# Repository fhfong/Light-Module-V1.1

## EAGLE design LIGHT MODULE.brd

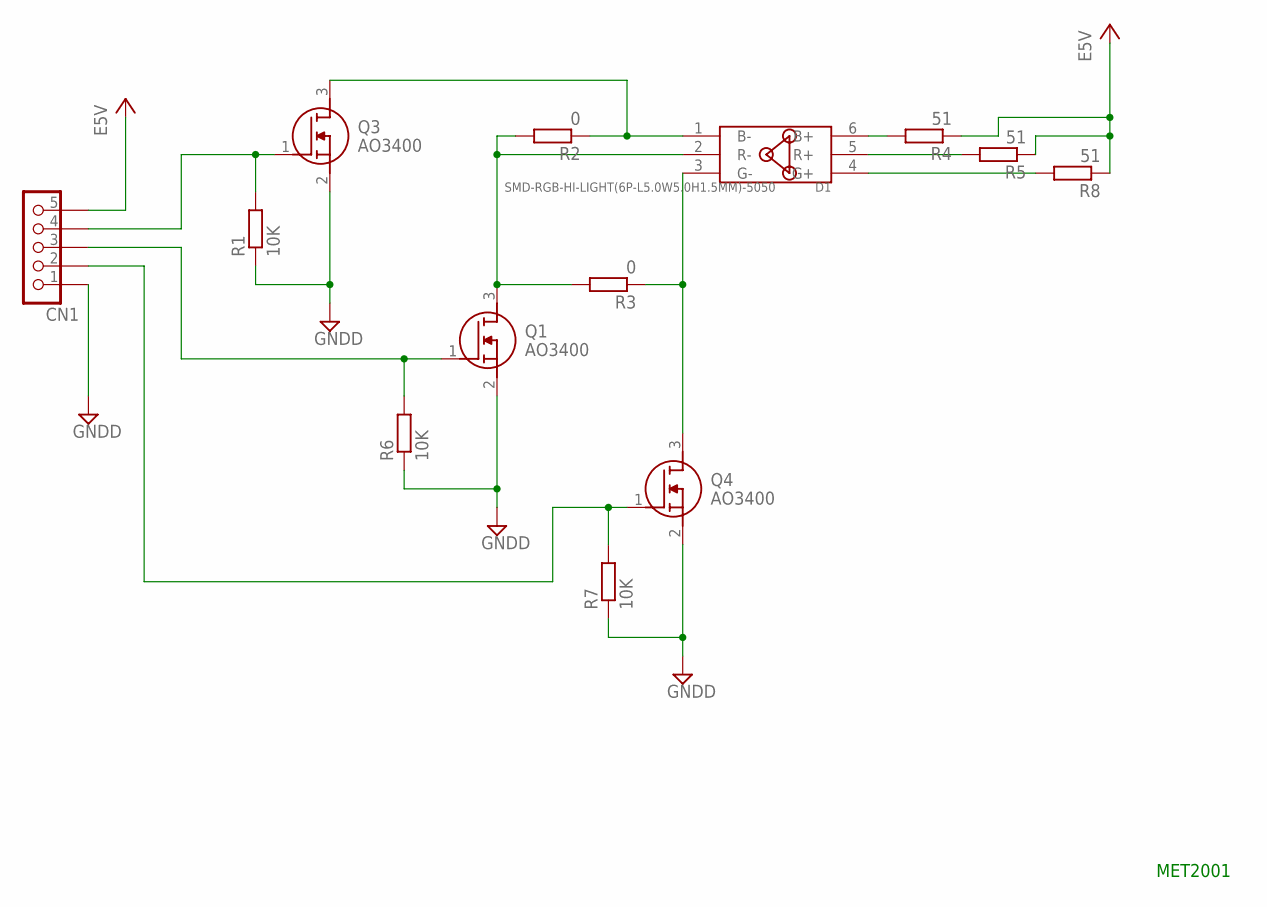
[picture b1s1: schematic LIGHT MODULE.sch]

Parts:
CN1: HEADER1X5; HEADER_1X5
D1: SMD-RGB-HI-LIGHT(6P-L5.0W5.0H1.5MM)-5050; LED6-SMD-5050
Q1, Q3, Q4: AO3400; SOT95P280X125-3N
R1, R6, R7: 10K; R0805
R2, R3: 0; R0805
R4, R5, R8: 51; R0805

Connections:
+5VA: CN1.5, R4.1, R5.1, R8.1
GNDD: CN1.1, Q1.2 (S), Q3.2 (S), Q4.2 (S), R1.1, R6.1, R7.1
unnamed: CN1.4, Q3.1 (G), R1.2
unnamed: D1.4 (G+), R8.2
unnamed: D1.5 (R+), R5.2
unnamed: D1.6 (B+), R4.2
unnamed: CN1.3, Q1.1 (G), R6.2
unnamed: D1.1 (B-), Q3.3 (D), R2.1
unnamed: D1.2 (R-), Q1.3 (D), R2.2, R3.2
unnamed: D1.3 (G-), Q4.3 (D), R3.1
unnamed: CN1.2, Q4.1 (G), R7.2

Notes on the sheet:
MET2001

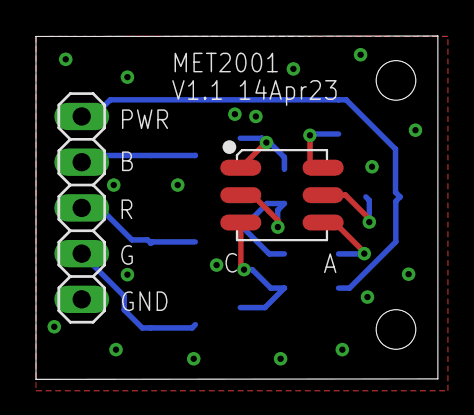
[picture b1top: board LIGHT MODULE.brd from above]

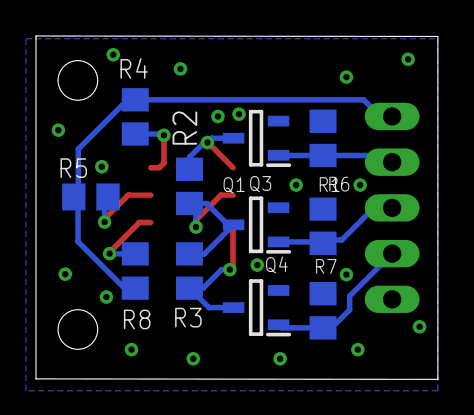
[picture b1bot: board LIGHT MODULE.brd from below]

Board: 2 copper layers, 22.3 x 19.1 mm, 13 parts (11 on the bottom side), 11 nets.

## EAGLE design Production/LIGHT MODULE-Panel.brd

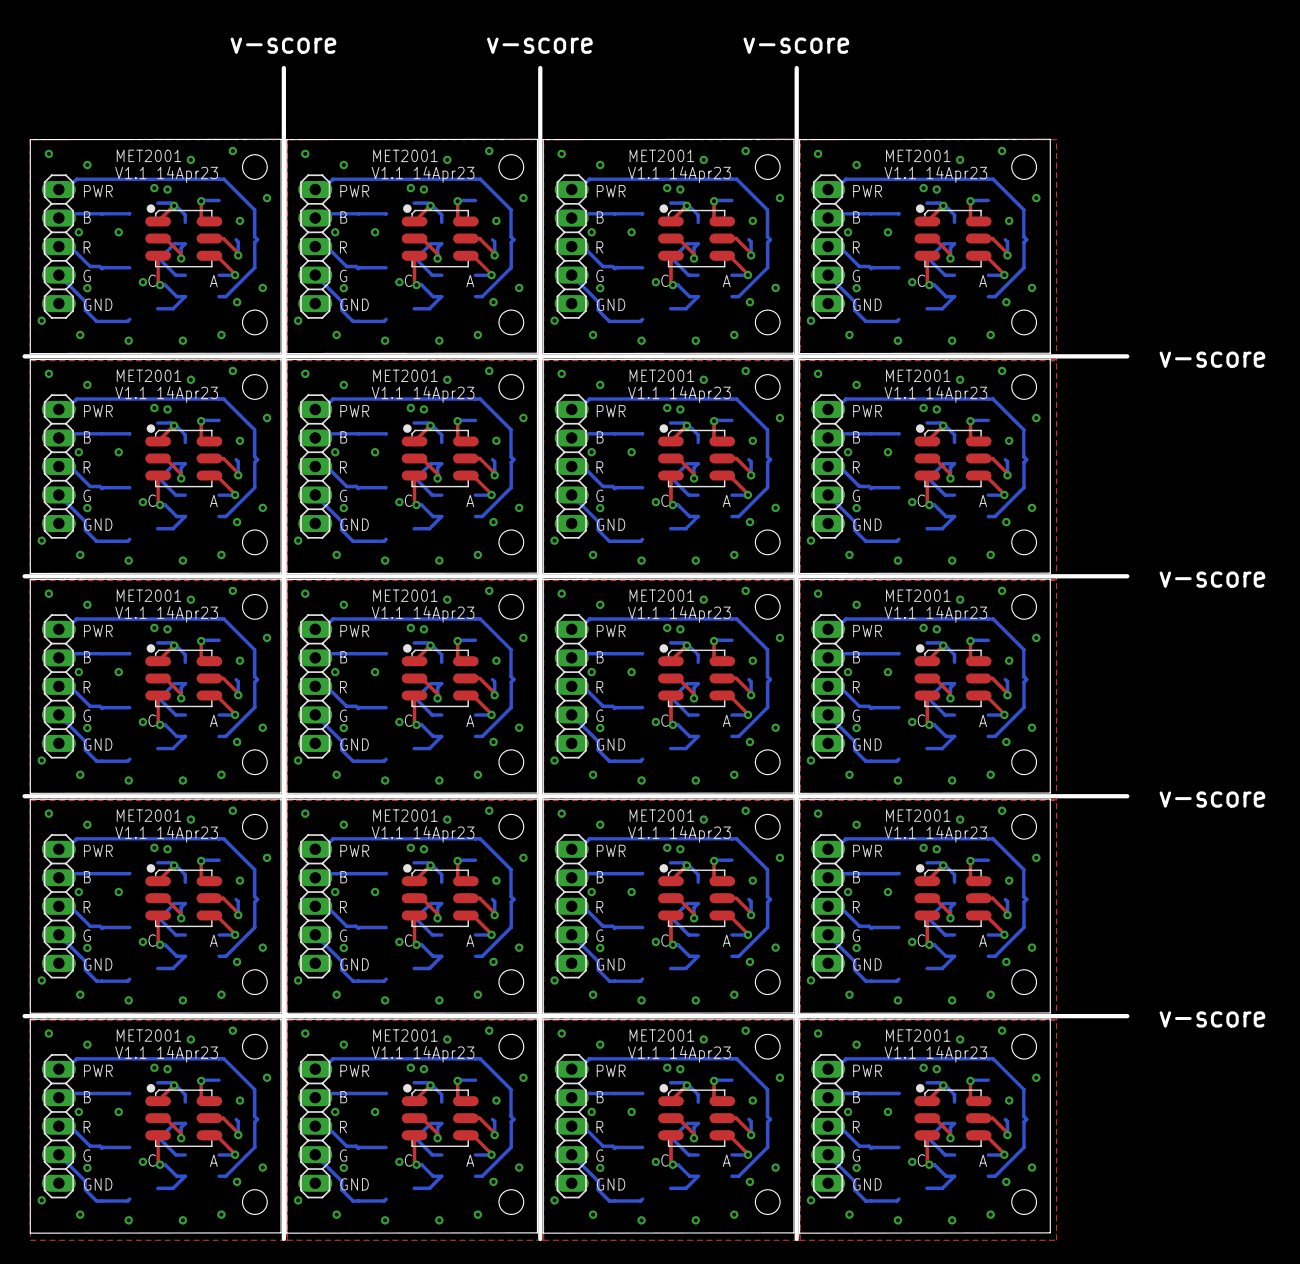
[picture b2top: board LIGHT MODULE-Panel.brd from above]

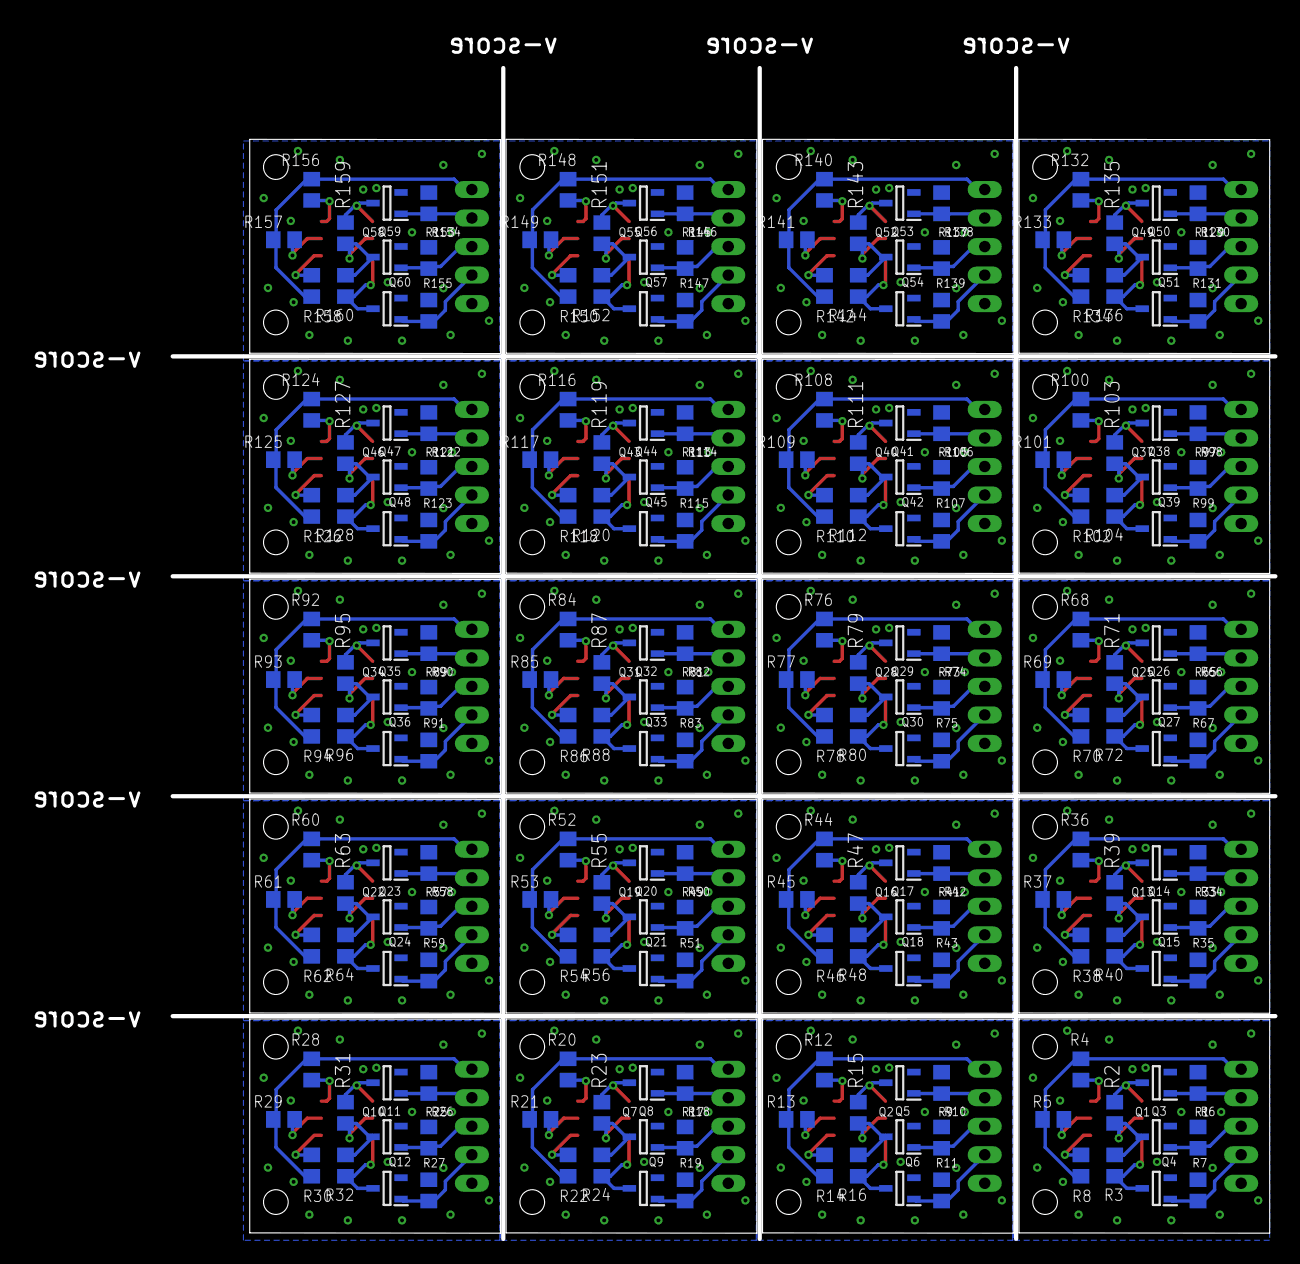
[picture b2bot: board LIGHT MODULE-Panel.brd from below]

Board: 2 copper layers, 111.4 x 108.1 mm, 260 parts (220 on the bottom side), 220 nets.

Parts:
CN1, CN2, CN3, CN4, CN5, CN6, CN7, CN8, CN9, CN10, CN11, CN12, CN13, CN14, CN15, CN16, CN17, CN18, CN19, CN20: HEADER_1X5
D1, D2, D3, D4, D5, D6, D7, D8, D9, D10, D11, D12, D13, D14, D15, D16, D17, D18, D19, D20: SMD-RGB-HI-LIGHT(6P-L5.0W5.0*H1.5MM)-5050; LED6-SMD-5050
Q1, Q2, Q3, Q4, Q5, Q6, Q7, Q8, Q9, Q10, Q11, Q12, Q13, Q14, Q15, Q16, Q17, Q18, Q19, Q20, Q21, Q22, Q23, Q24, Q25, Q26, Q27, Q28, Q29, Q30, Q31, Q32, Q33, Q34, Q35, Q36, Q37, Q38, Q39, Q40, Q41, Q42, Q43, Q44, Q45, Q46, Q47, Q48, Q49, Q50, Q51, Q52, Q53, Q54, Q55, Q56, Q57, Q58, Q59, Q60: AO3400; SOT95P280X125-3N
R1, R6, R7, R9, R10, R11, R17, R18, R19, R25, R26, R27, R33, R34, R35, R41, R42, R43, R49, R50, R51, R57, R58, R59, R65, R66, R67, R73, R74, R75, R81, R82, R83, R89, R90, R91, R97, R98, R99, R105, R106, R107, R113, R114, R115, R121, R122, R123, R129, R130, R131, R137, R138, R139, R145, R146, R147, R153, R154, R155: 10K; R0805
R2, R3, R15, R16, R23, R24, R31, R32, R39, R40, R47, R48, R55, R56, R63, R64, R71, R72, R79, R80, R87, R88, R95, R96, R103, R104, R111, R112, R119, R120, R127, R128, R135, R136, R143, R144, R151, R152, R159, R160: 0; R0805
R4, R5, R8, R12, R13, R14, R20, R21, R22, R28, R29, R30, R36, R37, R38, R44, R45, R46, R52, R53, R54, R60, R61, R62, R68, R69, R70, R76, R77, R78, R84, R85, R86, R92, R93, R94, R100, R101, R102, R108, R109, R110, R116, R117, R118, R124, R125, R126, R132, R133, R134, R140, R141, R142, R148, R149, R150, R156, R157, R158: 51; R0805

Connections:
+5VA: CN1.5, R4.1, R5.1, R8.1
+5VA1: CN2.5, R12.1, R13.1, R14.1
+5VA2: CN3.5, R20.1, R21.1, R22.1
+5VA3: CN4.5, R28.1, R29.1, R30.1
+5VA4: CN5.5, R36.1, R37.1, R38.1
+5VA5: CN6.5, R44.1, R45.1, R46.1
+5VA6: CN7.5, R52.1, R53.1, R54.1
+5VA7: CN8.5, R60.1, R61.1, R62.1
+5VA8: CN9.5, R68.1, R69.1, R70.1
+5VA9: CN10.5, R76.1, R77.1, R78.1
+5VA10: CN11.5, R84.1, R85.1, R86.1
+5VA11: CN12.5, R92.1, R93.1, R94.1
+5VA12: CN13.5, R100.1, R101.1, R102.1
+5VA13: CN14.5, R108.1, R109.1, R110.1
+5VA14: CN15.5, R116.1, R117.1, R118.1
+5VA15: CN16.5, R124.1, R125.1, R126.1
+5VA16: CN17.5, R132.1, R133.1, R134.1
+5VA17: CN18.5, R140.1, R141.1, R142.1
+5VA18: CN19.5, R148.1, R149.1, R150.1
+5VA19: CN20.5, R156.1, R157.1, R158.1
GNDD: CN1.1, Q1.2, Q3.2, Q4.2, R1.1, R6.1, R7.1
GNDD1: CN2.1, Q2.2, Q5.2, Q6.2, R9.1, R10.1, R11.1
GNDD2: CN3.1, Q7.2, Q8.2, Q9.2, R17.1, R18.1, R19.1
GNDD3: CN4.1, Q10.2, Q11.2, Q12.2, R25.1, R26.1, R27.1
GNDD4: CN5.1, Q13.2, Q14.2, Q15.2, R33.1, R34.1, R35.1
GNDD5: CN6.1, Q16.2, Q17.2, Q18.2, R41.1, R42.1, R43.1
GNDD6: CN7.1, Q19.2, Q20.2, Q21.2, R49.1, R50.1, R51.1
GNDD7: CN8.1, Q22.2, Q23.2, Q24.2, R57.1, R58.1, R59.1
GNDD8: CN9.1, Q25.2, Q26.2, Q27.2, R65.1, R66.1, R67.1
GNDD9: CN10.1, Q28.2, Q29.2, Q30.2, R73.1, R74.1, R75.1
GNDD10: CN11.1, Q31.2, Q32.2, Q33.2, R81.1, R82.1, R83.1
GNDD11: CN12.1, Q34.2, Q35.2, Q36.2, R89.1, R90.1, R91.1
GNDD12: CN13.1, Q37.2, Q38.2, Q39.2, R97.1, R98.1, R99.1
GNDD13: CN14.1, Q40.2, Q41.2, Q42.2, R105.1, R106.1, R107.1
GNDD14: CN15.1, Q43.2, Q44.2, Q45.2, R113.1, R114.1, R115.1
GNDD15: CN16.1, Q46.2, Q47.2, Q48.2, R121.1, R122.1, R123.1
GNDD16: CN17.1, Q49.2, Q50.2, Q51.2, R129.1, R130.1, R131.1
GNDD17: CN18.1, Q52.2, Q53.2, Q54.2, R137.1, R138.1, R139.1
GNDD18: CN19.1, Q55.2, Q56.2, Q57.2, R145.1, R146.1, R147.1
GNDD19: CN20.1, Q58.2, Q59.2, Q60.2, R153.1, R154.1, R155.1
unnamed: CN1.4, Q3.1, R1.2
unnamed: D1.4, R8.2
unnamed: D1.5, R5.2
unnamed: CN2.4, Q5.1, R9.2
unnamed: D1.6, R4.2
unnamed: CN1.3, Q1.1, R6.2
unnamed: D1.1, Q3.3, R2.1
unnamed: D1.2, Q1.3, R2.2, R3.2
unnamed: D1.3, Q4.3, R3.1
unnamed: CN2.3, Q2.1, R10.2
unnamed: D2.1, Q5.3, R15.1
unnamed: D2.2, Q2.3, R15.2, R16.2
unnamed: D2.3, Q6.3, R16.1
unnamed: CN2.2, Q6.1, R11.2
unnamed: CN1.2, Q4.1, R7.2
unnamed: D2.4, R14.2
unnamed: D2.5, R13.2
unnamed: D2.6, R12.2
unnamed: CN3.4, Q8.1, R17.2
unnamed: CN3.3, Q7.1, R18.2
unnamed: D3.1, Q8.3, R23.1
unnamed: D3.2, Q7.3, R23.2, R24.2
unnamed: D3.3, Q9.3, R24.1
unnamed: CN3.2, Q9.1, R19.2
unnamed: D3.4, R22.2
unnamed: D3.5, R21.2
unnamed: D3.6, R20.2
unnamed: CN4.4, Q11.1, R25.2
unnamed: CN4.3, Q10.1, R26.2
unnamed: D4.1, Q11.3, R31.1
unnamed: D4.2, Q10.3, R31.2, R32.2
unnamed: D4.3, Q12.3, R32.1
unnamed: CN4.2, Q12.1, R27.2
unnamed: D4.4, R30.2
unnamed: D4.5, R29.2
unnamed: D4.6, R28.2
unnamed: CN5.4, Q14.1, R33.2
unnamed: CN5.3, Q13.1, R34.2
unnamed: D5.1, Q14.3, R39.1
unnamed: D5.2, Q13.3, R39.2, R40.2
unnamed: D5.3, Q15.3, R40.1
unnamed: CN5.2, Q15.1, R35.2
unnamed: D5.4, R38.2
unnamed: D5.5, R37.2
unnamed: D5.6, R36.2
unnamed: CN6.4, Q17.1, R41.2
unnamed: CN6.3, Q16.1, R42.2
unnamed: D6.1, Q17.3, R47.1
unnamed: D6.2, Q16.3, R47.2, R48.2
unnamed: D6.3, Q18.3, R48.1
unnamed: CN6.2, Q18.1, R43.2
unnamed: D6.4, R46.2
unnamed: D6.5, R45.2
unnamed: D6.6, R44.2
unnamed: CN7.4, Q20.1, R49.2
unnamed: CN7.3, Q19.1, R50.2
unnamed: D7.1, Q20.3, R55.1
unnamed: D7.2, Q19.3, R55.2, R56.2
unnamed: D7.3, Q21.3, R56.1
unnamed: CN7.2, Q21.1, R51.2
unnamed: D7.4, R54.2
unnamed: D7.5, R53.2
unnamed: D7.6, R52.2
unnamed: CN8.4, Q23.1, R57.2
unnamed: CN8.3, Q22.1, R58.2
unnamed: D8.1, Q23.3, R63.1
unnamed: D8.2, Q22.3, R63.2, R64.2
unnamed: D8.3, Q24.3, R64.1
unnamed: CN8.2, Q24.1, R59.2
unnamed: D8.4, R62.2
unnamed: D8.5, R61.2
unnamed: D8.6, R60.2
unnamed: CN9.4, Q26.1, R65.2
unnamed: CN9.3, Q25.1, R66.2
unnamed: D9.1, Q26.3, R71.1
unnamed: D9.2, Q25.3, R71.2, R72.2
unnamed: D9.3, Q27.3, R72.1
unnamed: CN9.2, Q27.1, R67.2
unnamed: D9.4, R70.2
unnamed: D9.5, R69.2
unnamed: D9.6, R68.2
unnamed: CN10.4, Q29.1, R73.2
unnamed: CN10.3, Q28.1, R74.2
unnamed: D10.1, Q29.3, R79.1
unnamed: D10.2, Q28.3, R79.2, R80.2
unnamed: D10.3, Q30.3, R80.1
unnamed: CN10.2, Q30.1, R75.2
unnamed: D10.4, R78.2
unnamed: D10.5, R77.2
unnamed: D10.6, R76.2
unnamed: CN11.4, Q32.1, R81.2
unnamed: CN11.3, Q31.1, R82.2
unnamed: D11.1, Q32.3, R87.1
unnamed: D11.2, Q31.3, R87.2, R88.2
unnamed: D11.3, Q33.3, R88.1
unnamed: CN11.2, Q33.1, R83.2
unnamed: D11.4, R86.2
unnamed: D11.5, R85.2
unnamed: D11.6, R84.2
unnamed: CN12.4, Q35.1, R89.2
unnamed: CN12.3, Q34.1, R90.2
unnamed: D12.1, Q35.3, R95.1
unnamed: D12.2, Q34.3, R95.2, R96.2
unnamed: D12.3, Q36.3, R96.1
unnamed: CN12.2, Q36.1, R91.2
unnamed: D12.4, R94.2
unnamed: D12.5, R93.2
unnamed: D12.6, R92.2
unnamed: CN13.4, Q38.1, R97.2
unnamed: CN13.3, Q37.1, R98.2
unnamed: D13.1, Q38.3, R103.1
unnamed: D13.2, Q37.3, R103.2, R104.2
unnamed: D13.3, Q39.3, R104.1
unnamed: CN13.2, Q39.1, R99.2
unnamed: D13.4, R102.2
unnamed: D13.5, R101.2
unnamed: D13.6, R100.2
unnamed: CN14.4, Q41.1, R105.2
unnamed: CN14.3, Q40.1, R106.2
unnamed: D14.1, Q41.3, R111.1
unnamed: D14.2, Q40.3, R111.2, R112.2
unnamed: D14.3, Q42.3, R112.1
unnamed: CN14.2, Q42.1, R107.2
unnamed: D14.4, R110.2
unnamed: D14.5, R109.2
unnamed: D14.6, R108.2
unnamed: CN15.4, Q44.1, R113.2
unnamed: CN15.3, Q43.1, R114.2
unnamed: D15.1, Q44.3, R119.1
unnamed: D15.2, Q43.3, R119.2, R120.2
unnamed: D15.3, Q45.3, R120.1
unnamed: CN15.2, Q45.1, R115.2
unnamed: D15.4, R118.2
unnamed: D15.5, R117.2
unnamed: D15.6, R116.2
unnamed: CN16.4, Q47.1, R121.2
unnamed: CN16.3, Q46.1, R122.2
unnamed: D16.1, Q47.3, R127.1
unnamed: D16.2, Q46.3, R127.2, R128.2
unnamed: D16.3, Q48.3, R128.1
unnamed: CN16.2, Q48.1, R123.2
unnamed: D16.4, R126.2
unnamed: D16.5, R125.2
unnamed: D16.6, R124.2
unnamed: CN17.4, Q50.1, R129.2
unnamed: CN17.3, Q49.1, R130.2
unnamed: D17.1, Q50.3, R135.1
unnamed: D17.2, Q49.3, R135.2, R136.2
unnamed: D17.3, Q51.3, R136.1
unnamed: CN17.2, Q51.1, R131.2
unnamed: D17.4, R134.2
unnamed: D17.5, R133.2
unnamed: D17.6, R132.2
unnamed: CN18.4, Q53.1, R137.2
unnamed: CN18.3, Q52.1, R138.2
unnamed: D18.1, Q53.3, R143.1
unnamed: D18.2, Q52.3, R143.2, R144.2
unnamed: D18.3, Q54.3, R144.1
unnamed: CN18.2, Q54.1, R139.2
unnamed: D18.4, R142.2
unnamed: D18.5, R141.2
unnamed: D18.6, R140.2
unnamed: CN19.4, Q56.1, R145.2
unnamed: CN19.3, Q55.1, R146.2
unnamed: D19.1, Q56.3, R151.1
unnamed: D19.2, Q55.3, R151.2, R152.2
unnamed: D19.3, Q57.3, R152.1
unnamed: CN19.2, Q57.1, R147.2
unnamed: D19.4, R150.2
unnamed: D19.5, R149.2
unnamed: D19.6, R148.2
unnamed: CN20.4, Q59.1, R153.2
unnamed: CN20.3, Q58.1, R154.2
unnamed: D20.1, Q59.3, R159.1
unnamed: D20.2, Q58.3, R159.2, R160.2
unnamed: D20.3, Q60.3, R160.1
unnamed: CN20.2, Q60.1, R155.2
unnamed: D20.4, R158.2
unnamed: D20.5, R157.2
unnamed: D20.6, R156.2

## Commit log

2023-05-17 Light Module 1st commit
2023-05-17 Minor change to BOM details
